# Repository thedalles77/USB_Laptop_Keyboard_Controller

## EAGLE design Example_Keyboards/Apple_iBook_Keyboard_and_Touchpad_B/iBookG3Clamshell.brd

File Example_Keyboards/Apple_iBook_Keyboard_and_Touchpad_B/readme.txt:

These Eagle layouts are for an obsolete Teensy 3.2 cutout board so should not be used for new builds. 
The Teensy 3.2 code is for a G3 Clamshell keyboard and a Dell PS/2 touchpad (not the original clamshell touchpad).
For new builds that use the Teensy 4.0, go to the iBookG3_Clamshell folder for board layouts and keyboard code given here.
https://github.com/thedalles77/USB_Laptop_Keyboard_Controller/tree/master/Example_Keyboards/iBookG3_Clamshell

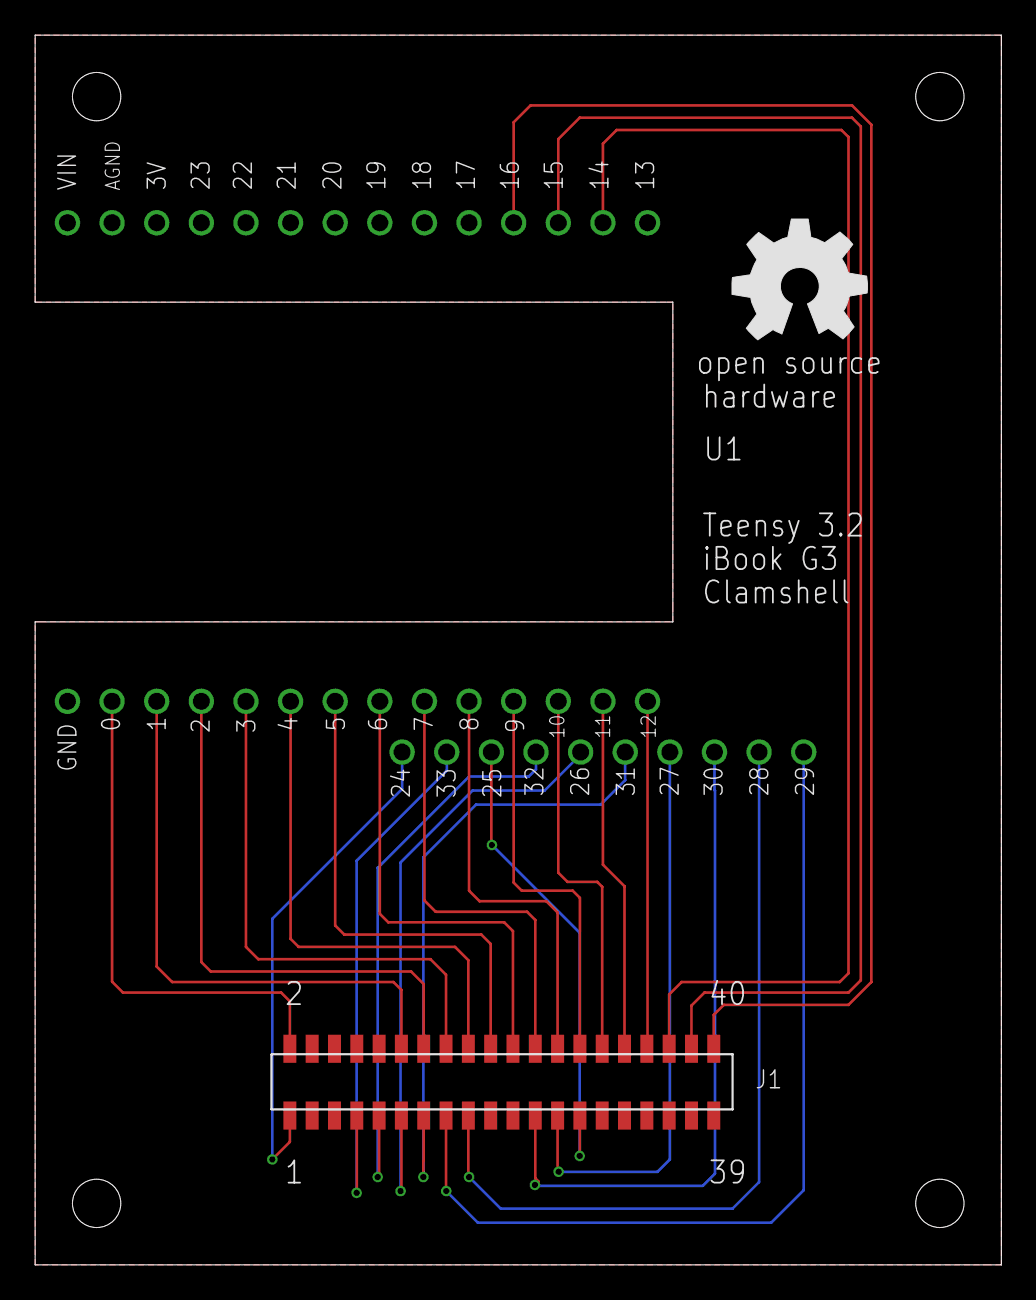
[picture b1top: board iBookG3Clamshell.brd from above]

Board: 2 copper layers, 55.0 x 70.0 mm, 3 parts (0 on the bottom side), 26 nets.

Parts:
J1: HDR127MET40FGVSMDR
U1: Teensy 3.2; TEENSY3P2CUTOUT
U$1: OSHW_8MM

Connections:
0: J1.P$2, U1.0
1: J1.P$12, U1.1
2: J1.P$14, U1.2
3: J1.P$16, U1.3
4: J1.P$18, U1.4
5: J1.P$20, U1.5
6: J1.P$22, U1.6
7: J1.P$24, U1.7
8: J1.P$26, U1.8
9: J1.P$28, U1.9
10: J1.P$30, U1.10
11: J1.P$32, U1.11
12: J1.P$34, U1.12
14: J1.P$36, U1.14
15: J1.P$38, U1.15
16: J1.P$40, U1.16
24: J1.P$1, U1.24
25: J1.P$27, U1.25
26: J1.P$11, U1.26
27: J1.P$25, U1.27
28: J1.P$17, U1.28
29: J1.P$15, U1.29
30: J1.P$23, U1.30
31: J1.P$13, U1.31
32: J1.P$9, U1.32
33: J1.P$7, U1.33

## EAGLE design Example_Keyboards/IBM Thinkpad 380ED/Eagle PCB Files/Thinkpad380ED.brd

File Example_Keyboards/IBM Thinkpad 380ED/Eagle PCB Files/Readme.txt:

To fabricate at OSHPark.com, send the .brd file to them. It will cost about $27 to fabricate 3 boards (includes USPS shipping in the US).

To fabricate at JLCPCB.com, send the .zip file to them. It will cost about $8 to fabricate and slow ship 5 boards to the US.

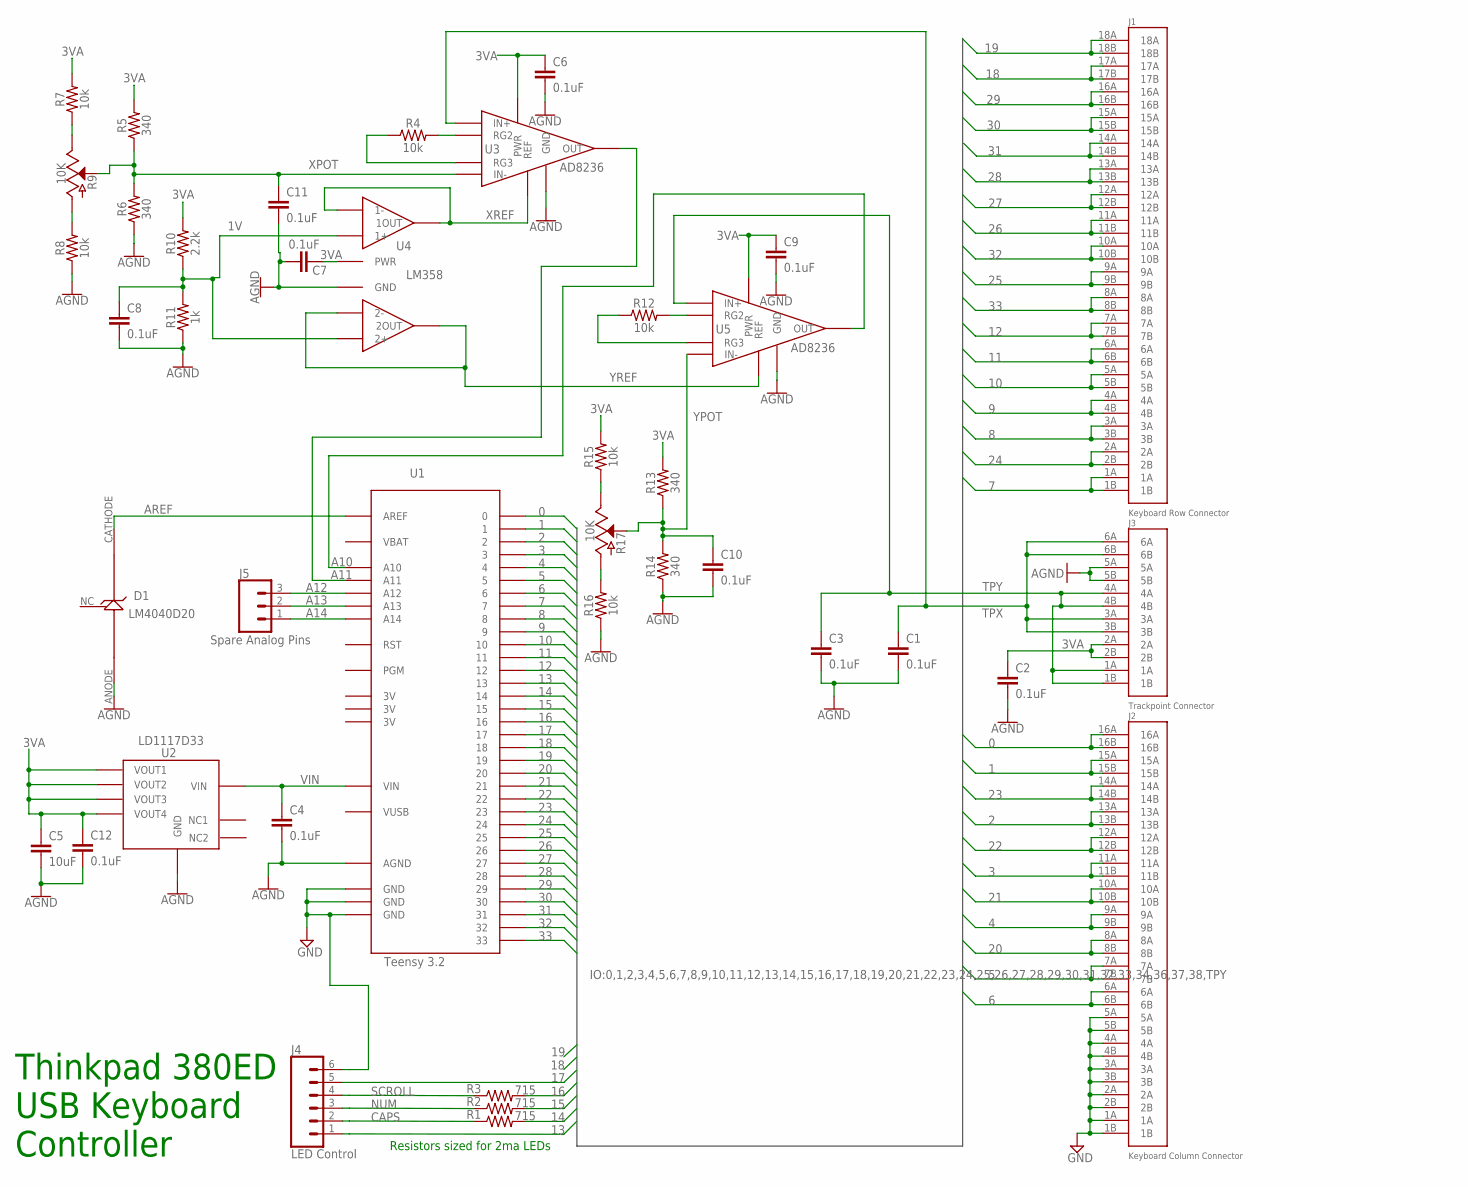
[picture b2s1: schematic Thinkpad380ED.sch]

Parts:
C1, C2, C3, C4, C6, C7, C8, C9, C10, C11, C12: 0.1uF; 0603
C5: 10uF; 0603
D1: LM4040D20; LM4040
J1: Keyboard Row Connector; 0526101833
J2: Keyboard Column Connector; 0526101633
J3: Trackpoint Connector; 0526100633
J4: LED Control; 1X06
J5: Spare Analog Pins; 1X03
R1, R2, R3: 715; 0603
R4, R7, R8, R12, R15, R16: 10k; 0603
R5, R6, R13, R14: 340; 0603
R9, R17: 10K; 3296W-1-103LF
R10: 2.2k; 0603
R11: 1k; 0603
U1: Teensy 3.2; TEENSY_3P2
U2: LD1117D33; LD1117D33CTR
U3, U5: AD8236
U4: LM358; LM358D

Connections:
0: J2.16A, J2.16B, U1.0
1: J2.15A, J2.15B, U1.1
1V: C8.1, R10.1, R11.2, U4.IN1+ (1+), U4.IN2+ (2+)
2: J2.13A, J2.13B, U1.2
3: J2.11A, J2.11B, U1.3
3VA: C2.1, C5.1, C6.1, C7.1, C9.1, C12.1, J3.2A, J3.2B, R5.2, R7.2, R10.2, R13.2, R15.2, U2.VOUT1, U2.VOUT2, U2.VOUT3, U2.VOUT4, U3.PWR, U4.PWR, U5.PWR
4: J2.9A, J2.9B, U1.4
5: J2.7A, J2.7B, U1.5
6: J2.6A, J2.6B, U1.6
7: J1.1A, J1.1B, U1.7
8: J1.3A, J1.3B, U1.8
9: J1.4A, J1.4B, U1.9
10: J1.5A, J1.5B, U1.10
11: J1.6A, J1.6B, U1.11
12: J1.7A, J1.7B, U1.12
13: J4.1, U1.13
14: R1.2, U1.14
15: R2.2, U1.15
16: R3.2, U1.16
17: J4.5, U1.17
18: J1.17A, J1.17B, U1.18
19: J1.18A, J1.18B, U1.19
20: J2.8A, J2.8B, U1.20
21: J2.10A, J2.10B, U1.21
22: J2.12A, J2.12B, U1.22
23: J2.14A, J2.14B, U1.23
24: J1.2A, J1.2B, U1.24
25: J1.9A, J1.9B, U1.25
26: J1.11A, J1.11B, U1.26
27: J1.12A, J1.12B, U1.27
28: J1.13A, J1.13B, U1.28
29: J1.16A, J1.16B, U1.29
30: J1.15A, J1.15B, U1.30
31: J1.14A, J1.14B, U1.31
32: J1.10A, J1.10B, U1.32
33: J1.8A, J1.8B, U1.33
A10: U1.A10, U5.VOUT (OUT)
A11: U1.A11, U3.VOUT (OUT)
A12: J5.3, U1.A12
A13: J5.2, U1.A13
A14: J5.1, U1.A14
AGND: C1.2, C2.2, C3.2, C4.2, C5.2, C6.2, C7.2, C8.2, C9.2, C10.2, C11.2, C12.2, D1.ANODE, J3.5A, J3.5B, R6.1, R8.1, R11.1, R14.1, R16.1, U1.AGND, U2.GND, U3.GND, U4.GND, U5.GND
AREF: D1.CATHODE, U1.AREF
CAPS: J4.2, R1.1
GND: J2.1A, J2.1B, J2.2A, J2.2B, J2.3A, J2.3B, J2.4A, J2.4B, J2.5A, J2.5B, J4.6, U1.GND1 (GND), U1.GND2 (GND), U1.GND3 (GND)
unnamed: R4.2, U3.RG2
unnamed: R4.1, U3.RG3
unnamed: R8.2, R9.A
unnamed: R7.1, R9.E
unnamed: R12.2, U5.RG2
unnamed: R12.1, U5.RG3
unnamed: R16.2, R17.A
unnamed: R15.1, R17.E
NUM: J4.3, R2.1
SCROLL: J4.4, R3.1
TPX: C1.1, J3.3A, J3.3B, J3.6A, J3.6B, U3.IN+
TPY: C3.1, J3.1A, J3.1B, J3.4A, J3.4B, U5.IN+
VIN: C4.1, U1.VIN, U2.VIN
XPOT: C11.1, R5.1, R6.2, R9.S, U3.IN-
XREF: U3.REF, U4.IN1- (1-), U4.OUT1 (1OUT)
YPOT: C10.1, R13.1, R14.2, R17.S, U5.IN-
YREF: U4.IN2- (2-), U4.OUT2 (2OUT), U5.REF

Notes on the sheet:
Thinkpad 380ED USB Keyboard Controller
Resistors sized for 2ma LEDs

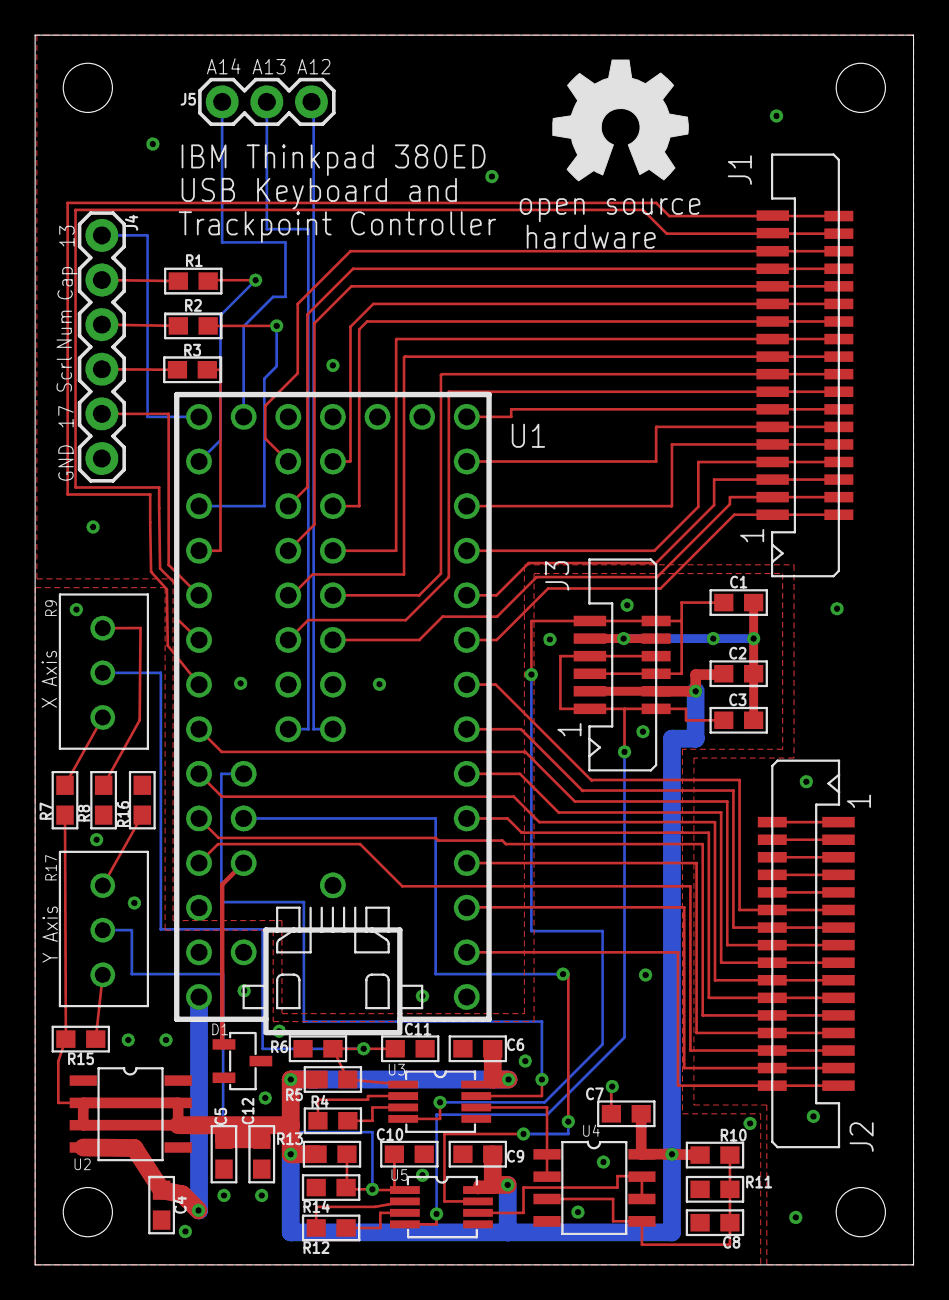
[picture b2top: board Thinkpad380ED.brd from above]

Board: 2 copper layers, 50.0 x 70.0 mm, 41 parts (0 on the bottom side), 62 nets.

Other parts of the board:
U$1: OSHW_8MM

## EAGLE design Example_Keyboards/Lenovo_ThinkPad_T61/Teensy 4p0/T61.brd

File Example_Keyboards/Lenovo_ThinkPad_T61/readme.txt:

These folders are for a Teensy T61 Thinkpad keyboard controller.

For a Raspberry Pi Pico T61 Thinkpad keyboard controller, go to this folder instead:
https://github.com/thedalles77/USB_Laptop_Keyboard_Controller/tree/master/Example_Keyboards/Pico_T61_Keyboard

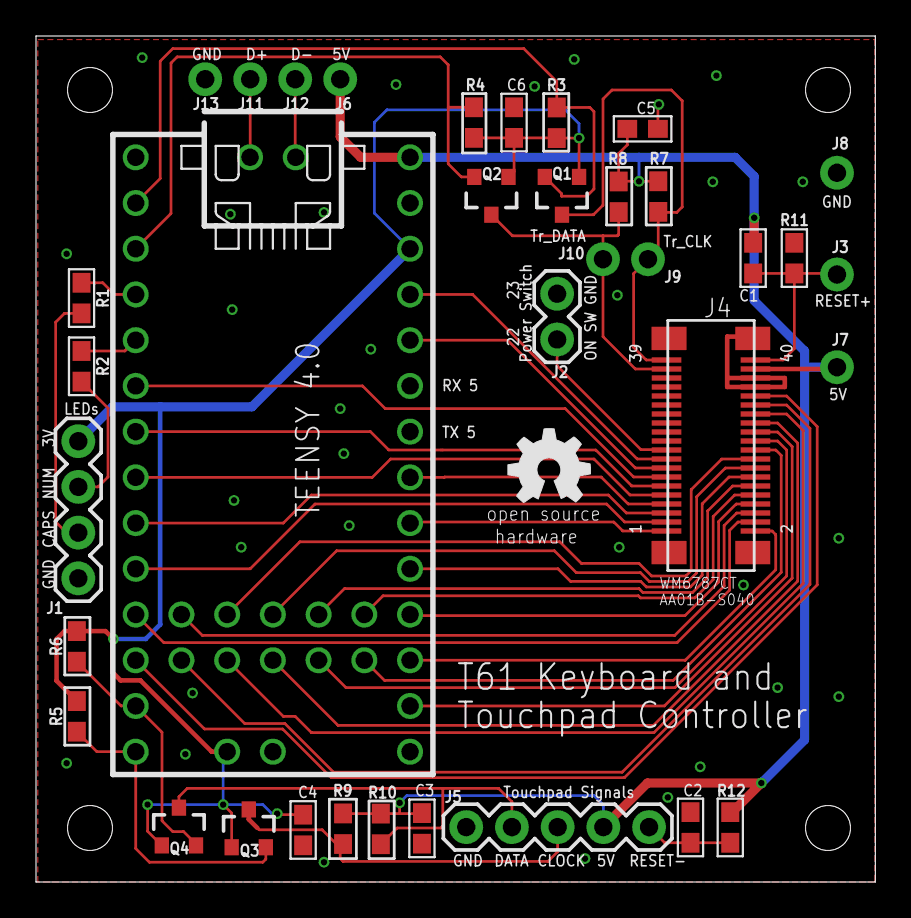
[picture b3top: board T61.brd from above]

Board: 2 copper layers, 46.6 x 47.0 mm, 38 parts (0 on the bottom side), 45 nets.

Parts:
C1, C2: 2.2UF; 0603_CAP
C3, C4, C5, C6: 0.1uf; 0603_CAP
J1: LEDs; 1X04
J2: Power Switch; 1X02
J3: RESET+; 1X01_NO_SILK
J4: AA01B-S040; WM6787_AA01B
J5: Touchpad_Signals; 1X05
J6, J7: 5V; 1X01_NO_SILK
J8, J13: GND; 1X01_NO_SILK
J9: TP_CLK; 1X01_NO_SILK
J10: TP_DATA; 1X01_NO_SILK
J11: D+; 1X01_NO_SILK
J12: D-; 1X01_NO_SILK
Q1, Q2, Q3, Q4: 220mA/50V/3.5Ω; SOT23-3
R1, R2: 715; 0603
R3, R4, R5, R6, R7, R8, R9, R10: 4.7k; 0603
R11: 100K; 0603_RESISTOR
R12: 17K; 0603_RESISTOR
U1: TEENSY4P0
U$1: OSHW_5MM
U$2: OSHW_16MM

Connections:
0: Q1.2, R3.1, U1.0
1: Q2.2, R4.1, U1.1
2: R1.1, U1.2
3: R2.1, U1.3
3V: C4.1, C6.1, J1.4, Q1.1, Q2.1, Q3.1, Q4.1, R3.2, R4.2, R5.2, R6.2, U1.3V, U1.3V1
4: J4.P$13, U1.4
5: J4.P$11, U1.5
5V: C1.1, C3.1, C5.1, J4.P$38, J5.4, J6.1, J7.1, R7.2, R8.2, R9.2, R10.2, R12.2, U1.5V
6: J4.P$9, U1.6
7: J4.P$5, U1.7
8: J4.P$3, U1.8
9: J4.P$4, U1.9
10: J4.P$32, U1.10
11: Q4.2, R6.1, U1.11
12: Q3.2, R5.1, U1.12
14: J4.P$24, U1.14
15: J4.P$2, U1.15
16: J4.P$8, U1.16
17: J4.P$14, U1.17
18: J4.P$1, U1.18
19: J4.P$7, U1.19
22: J4.P$15, U1.22
23: J4.P$17, U1.23
24: J4.P$20, U1.24
25: J4.P$10, U1.25
26: J4.P$22, U1.26
27: J4.P$12, U1.27
28: J4.P$26, U1.28
29: J4.P$16, U1.29
30: J4.P$28, U1.30
31: J4.P$18, U1.31
32: J4.P$30, U1.32
33: J4.P$6, U1.33
CAPS_LOCK: J1.2, R1.2
D+: J11.1, U1.D+
D-: J12.1, U1.D-
GND: C2.2, C3.2, C4.2, C5.2, C6.2, J1.1, J2.1, J4.P$31, J4.P$34, J4.P$36, J4.TAB1, J4.TAB2, J4.TAB3, J4.TAB4, J5.1, J8.1, J13.1, R11.1, U1.GND1, U1.GND2, U1.GND3
NUM_LOCK: J1.3, R2.2
ON: J2.2, J4.P$19
PAD_CLOCK: J5.3, Q3.3, R9.1
PAD_DATA: J5.2, Q4.3, R10.1
RESET+: C1.2, J3.1, J4.P$40, R11.2
RESET-: C2.1, J5.5, R12.1
TP_CLK: J4.P$39, J9.1, Q1.3, R7.1
TP_DATA: J4.P$37, J10.1, Q2.3, R8.1

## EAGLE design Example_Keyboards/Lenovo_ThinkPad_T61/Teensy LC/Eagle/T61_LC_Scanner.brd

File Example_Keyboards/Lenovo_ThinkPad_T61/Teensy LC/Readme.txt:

The Teensy LC is obsolete. Use the Teensy 4p0 for new builds.

The Lenovo_T61_keyboard_LC.ino code is just for the keyboard. Once you get it working, try the keyboard and TP (combined) code. 
If there's a problem communicating with the TP, it can make the keyboard code erratic and not work. Debug the TP connection problems separately.

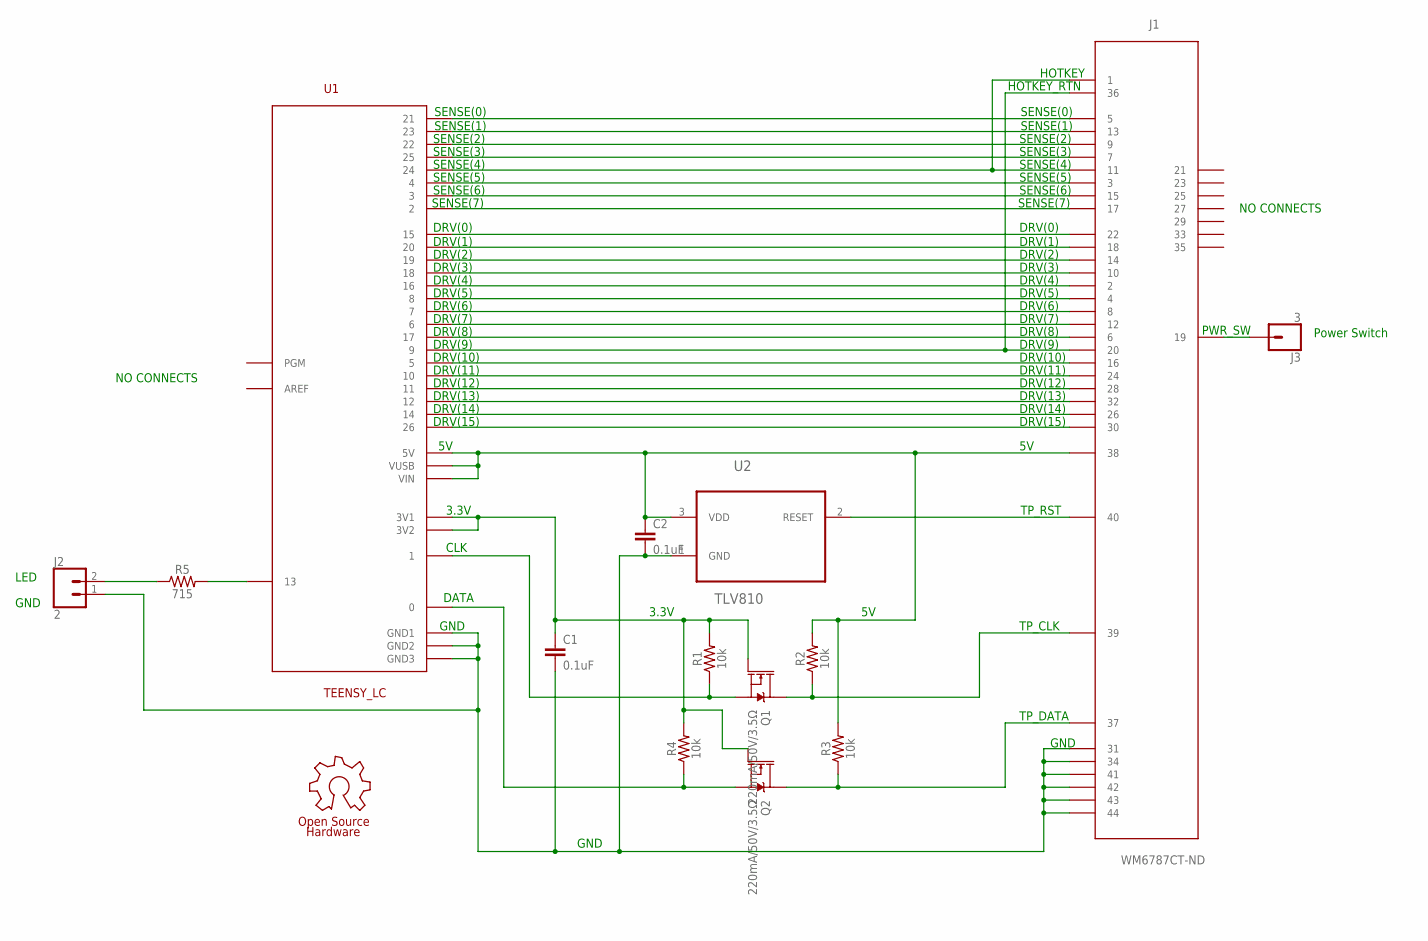
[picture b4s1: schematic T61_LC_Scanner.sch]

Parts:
C1, C2: 0.1uF; 0603
GOLD_ORB_SM1: OSHWLOGOLOGO5MM; OSHW_5MM
J1: WM6787CT-ND
J2: 2; 1X02
J3: 3; 1X01
Q1, Q2: 220mA/50V/3.5Ω; SOT23-3
R1, R2, R3, R4: 10k; 0603
R5: 715; 0603
U1: TEENSY_LC
U2: TLV810SDBZT; SOT95P237X112-3N

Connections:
3V: C1.1, Q1.1 (G), Q2.1 (G), R1.2, R4.2, U1.3V1, U1.3V2
5V: C2.1, J1.P$38 (38), R2.2, R3.2, U1.5V, U1.VIN, U1.VUSB, U2.3 (VDD)
CAPS_LCK: J2.2, R5.1
CLK: Q1.2 (S), R1.1, U1.1
DATA: Q2.2 (S), R4.1, U1.0
DRV(9): J1.P$20 (20), J1.P$36 (36), U1.9
GND: C1.2, C2.2, J1.P$31 (31), J1.P$34 (34), J1.P$41 (43), J1.P$42 (44), J1.P$43 (41), J1.P$44 (42), J2.1, U1.GND1, U1.GND2, U1.GND3, U2.1 (GND)
LED_13: R5.2, U1.13
unnamed: J1.P$5 (5), U1.21
unnamed: J1.P$13 (13), U1.23
unnamed: J1.P$9 (9), U1.22
unnamed: J1.P$7 (7), U1.25
unnamed: J1.P$3 (3), U1.4
unnamed: J1.P$15 (15), U1.3
unnamed: J1.P$17 (17), U1.2
unnamed: J1.P$22 (22), U1.15
unnamed: J1.P$18 (18), U1.20
unnamed: J1.P$14 (14), U1.19
unnamed: J1.P$10 (10), U1.18
unnamed: J1.P$2 (2), U1.16
unnamed: J1.P$4 (4), U1.8
unnamed: J1.P$8 (8), U1.7
unnamed: J1.P$12 (12), U1.6
unnamed: J1.P$6 (6), U1.17
unnamed: J1.P$16 (16), U1.5
unnamed: J1.P$24 (24), U1.10
unnamed: J1.P$28 (28), U1.11
unnamed: J1.P$32 (32), U1.12
unnamed: J1.P$26 (26), U1.14
unnamed: J1.P$30 (30), U1.26
PWR_SW: J1.P$19 (19), J3.1
SENSE(4): J1.P$1 (1), J1.P$11 (11), U1.24
TP_CLK: J1.P$39 (39), Q1.3 (D), R2.1
TP_DATA: J1.P$37 (37), Q2.3 (D), R3.1
TP_RST: J1.P$40 (40), U2.2 (RESET)

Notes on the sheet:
Power Switch
LED
GND
HOTKEY
HOTKEY_RTN
SENSE(0)
SENSE(1)
SENSE(2)
SENSE(3)
SENSE(4)
SENSE(5)
SENSE(6)
SENSE(7)
DRV(0)
DRV(1)
DRV(2)
DRV(3)
DRV(4)
DRV(5)
DRV(6)
DRV(7)
DRV(8)
DRV(9)
DRV(10)
DRV(11)
DRV(12)
DRV(13)
DRV(14)
DRV(15)
TP_RST
TP_CLK
TP_DATA
NO CONNECTS
PWR_SW
DATA
CLK
3.3V

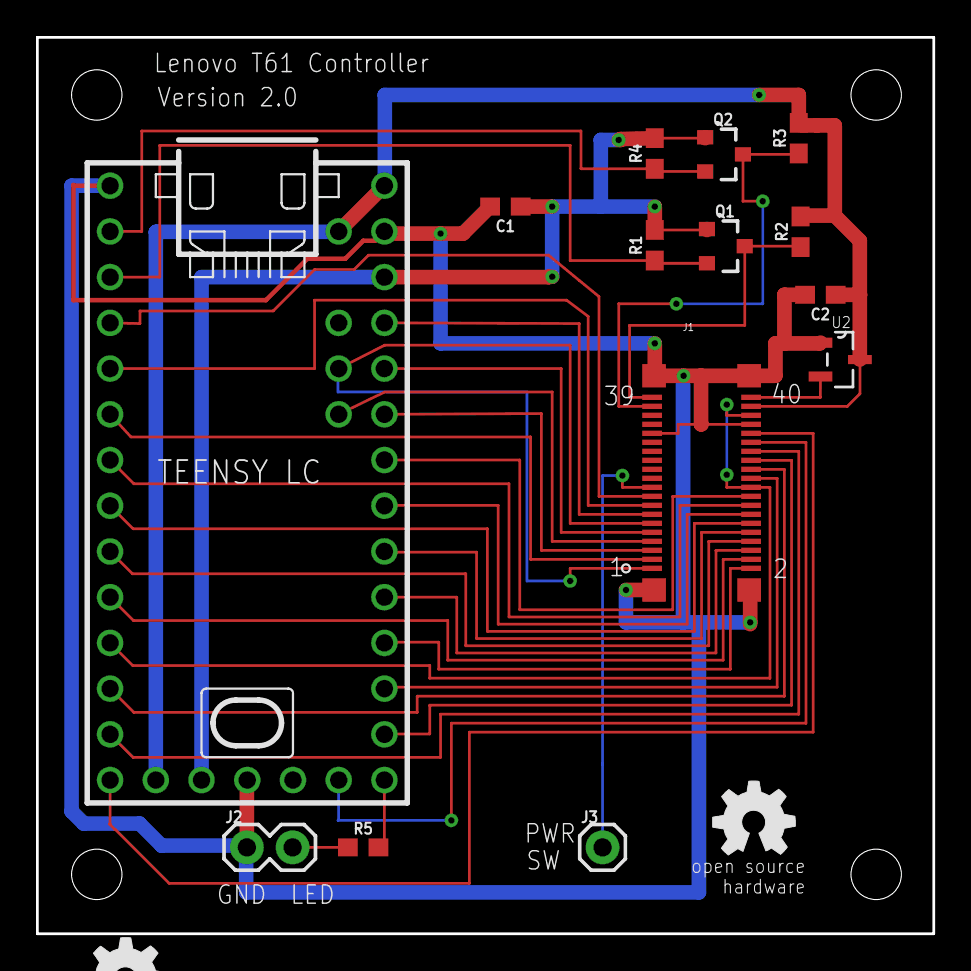
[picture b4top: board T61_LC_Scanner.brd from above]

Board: 2 copper layers, 49.8 x 49.8 mm, 16 parts (0 on the bottom side), 35 nets.

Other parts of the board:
U$1: OSHW_5MM

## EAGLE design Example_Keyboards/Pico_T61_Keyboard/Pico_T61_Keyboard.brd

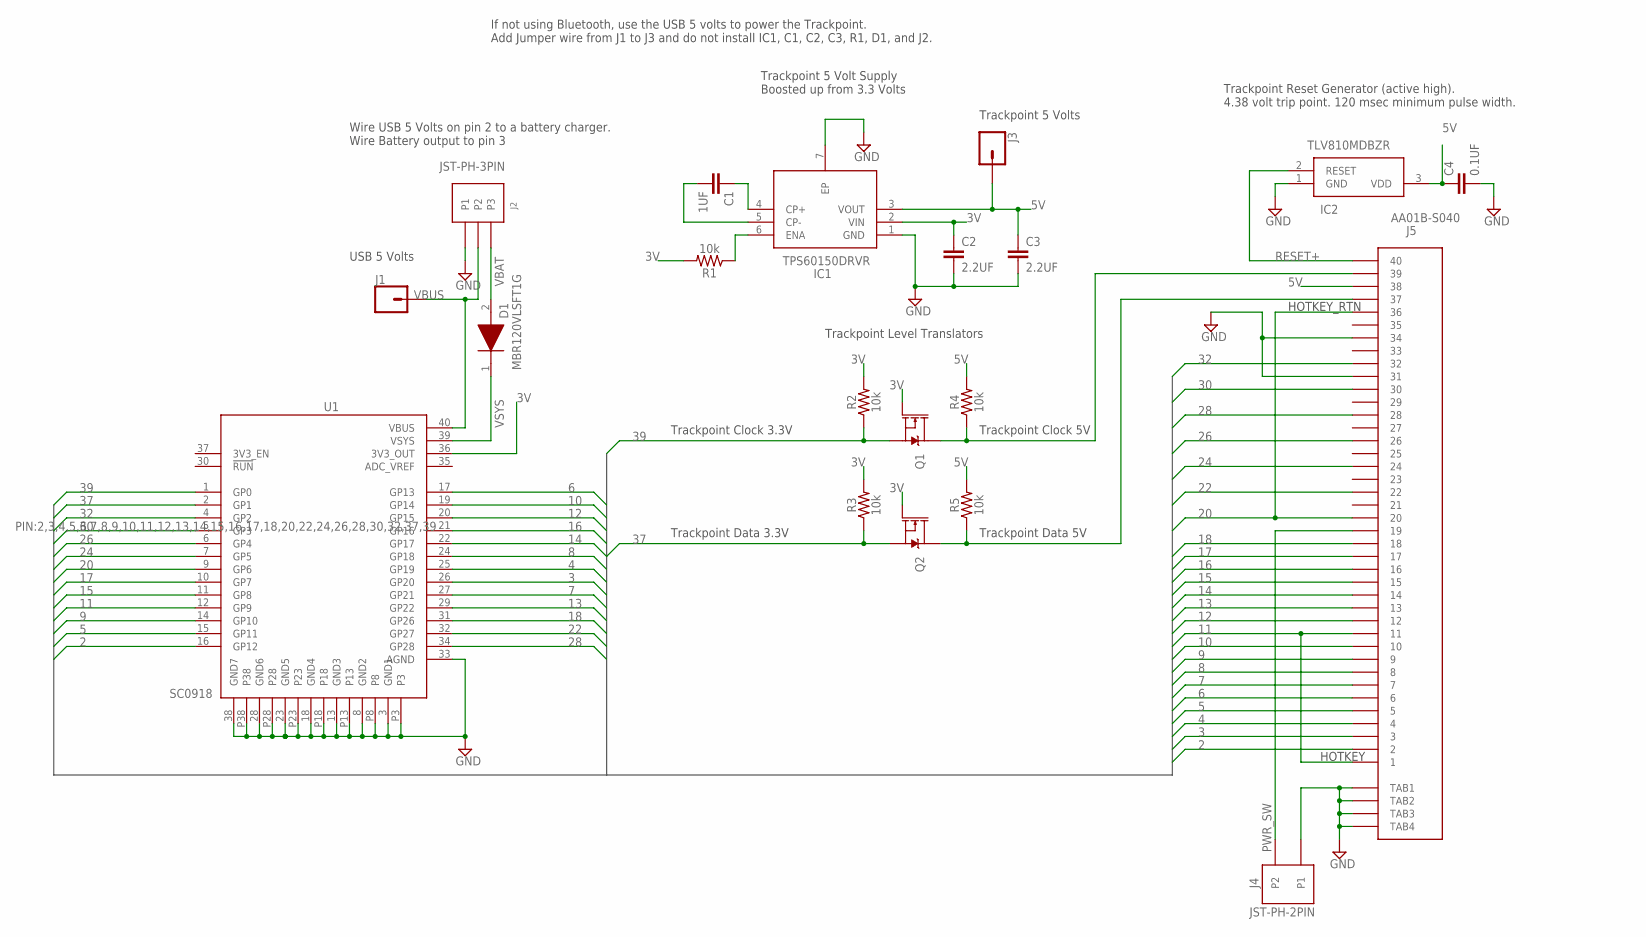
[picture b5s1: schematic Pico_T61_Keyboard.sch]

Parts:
C1: 1UF; 0603_CAP
C2, C3: 2.2UF; 0603_CAP
C4: 0.1UF; 0603_CAP
D1: MBR120VLSFT1G; SODFL3616X98N
IC1: TPS60150DRVR; SON65P200X200X80-7N
IC2: TLV810MDBZR; SOT95P237X112-3N
J1, J3: CONN_01PTH_NO_SILK_KIT; 1X01NS_KIT
J2: JST-PH-3PIN
J4: JST-PH-2PIN
J5: AA01B-S040; WM6787_AA01B
Q1, Q2: 220mA/50V/3.5Ω; SOT23-3
R1, R2, R3, R4, R5: 10k; 0603
U1: SC0918; MODULE_SC0918

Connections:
2: J5.P$2 (2), U1.16 (GP12)
3: J5.P$3 (3), U1.26 (GP20)
3V: C2.1, IC1.2 (VIN), Q1.1 (G), Q2.1 (G), R1.2, R2.2, R3.2, U1.36 (3V3_OUT)
4: J5.P$4 (4), U1.25 (GP19)
5: J5.P$5 (5), U1.15 (GP11)
5V: C3.1, C4.1, IC1.3 (VOUT), IC2.3 (VDD), J3.1, J5.P$38 (38), R4.2, R5.2
6: J5.P$6 (6), U1.17 (GP13)
7: J5.P$7 (7), U1.27 (GP21)
8: J5.P$8 (8), U1.24 (GP18)
9: J5.P$9 (9), U1.14 (GP10)
10: J5.P$10 (10), U1.19 (GP14)
11: J5.P$1 (1), J5.P$11 (11), U1.12 (GP9)
12: J5.P$12 (12), U1.20 (GP15)
13: J5.P$13 (13), U1.29 (GP22)
14: J5.P$14 (14), U1.22 (GP17)
15: J5.P$15 (15), U1.11 (GP8)
16: J5.P$16 (16), U1.21 (GP16)
17: J5.P$17 (17), U1.10 (GP7)
18: J5.P$18 (18), U1.31 (GP26)
20: J5.P$20 (20), J5.P$36 (36), U1.9 (GP6)
22: J5.P$22 (22), U1.32 (GP27)
24: J5.P$24 (24), U1.7 (GP5)
26: J5.P$26 (26), U1.6 (GP4)
28: J5.P$28 (28), U1.34 (GP28)
30: J5.P$30 (30), U1.5 (GP3)
32: J5.P$32 (32), U1.4 (GP2)
37: Q2.2 (S), R3.1, U1.2 (GP1)
39: Q1.2 (S), R2.1, U1.1 (GP0)
ADC_VREF: U1.35 (ADC_VREF)
GND: C2.2, C3.2, C4.2, IC1.1 (GND), IC1.7 (EP), IC2.1 (GND), J2.P$1 (P1), J4.P$1 (P1), J5.P$31 (31), J5.P$34 (34), J5.TAB1, J5.TAB2, J5.TAB3, J5.TAB4, U1.3 (GND1), U1.8 (GND2), U1.13 (GND3), U1.18 (GND4), U1.23 (GND5), U1.28 (GND6), U1.33 (AGND), U1.38 (GND7), U1.P3, U1.P8, U1.P13, U1.P18, U1.P23, U1.P28, U1.P38
unnamed: C1.1, IC1.4 (CP+)
unnamed: C1.2, IC1.5 (CP-)
unnamed: IC1.6 (ENA), R1.1
PWR_SW: J4.P$2 (P2), J5.P$19 (19)
RESET+: IC2.2 (RESET), J5.P$40 (40)
TP_CLK: J5.P$39 (39), Q1.3 (D), R4.1
TP_DATA: J5.P$37 (37), Q2.3 (D), R5.1
VBAT: D1.2 (A), J2.P$3 (P3)
VBUS: J1.1, J2.P$2 (P2), U1.40 (VBUS)
VSYS: D1.1 (K), U1.39 (VSYS)

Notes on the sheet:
Trackpoint Clock 3.3V
Trackpoint Data 3.3V
Trackpoint Clock 5V
Trackpoint Data 5V
Trackpoint Level Translators
HOTKEY
HOTKEY_RTN
Trackpoint 5 Volt Supply Boosted up from 3.3 Volts
Trackpoint Reset Generator (active high). 4.38 volt trip point. 120 msec minimum pulse width.
Wire USB 5 Volts on pin 2 to a battery charger. Wire Battery output to pin 3
USB 5 Volts
Trackpoint 5 Volts
If not using Bluetooth, use the USB 5 volts to power the Trackpoint. Add Jumper wire from J1 to J3 and do not install IC1, C1, C2, C3, R1, D1, and J2.

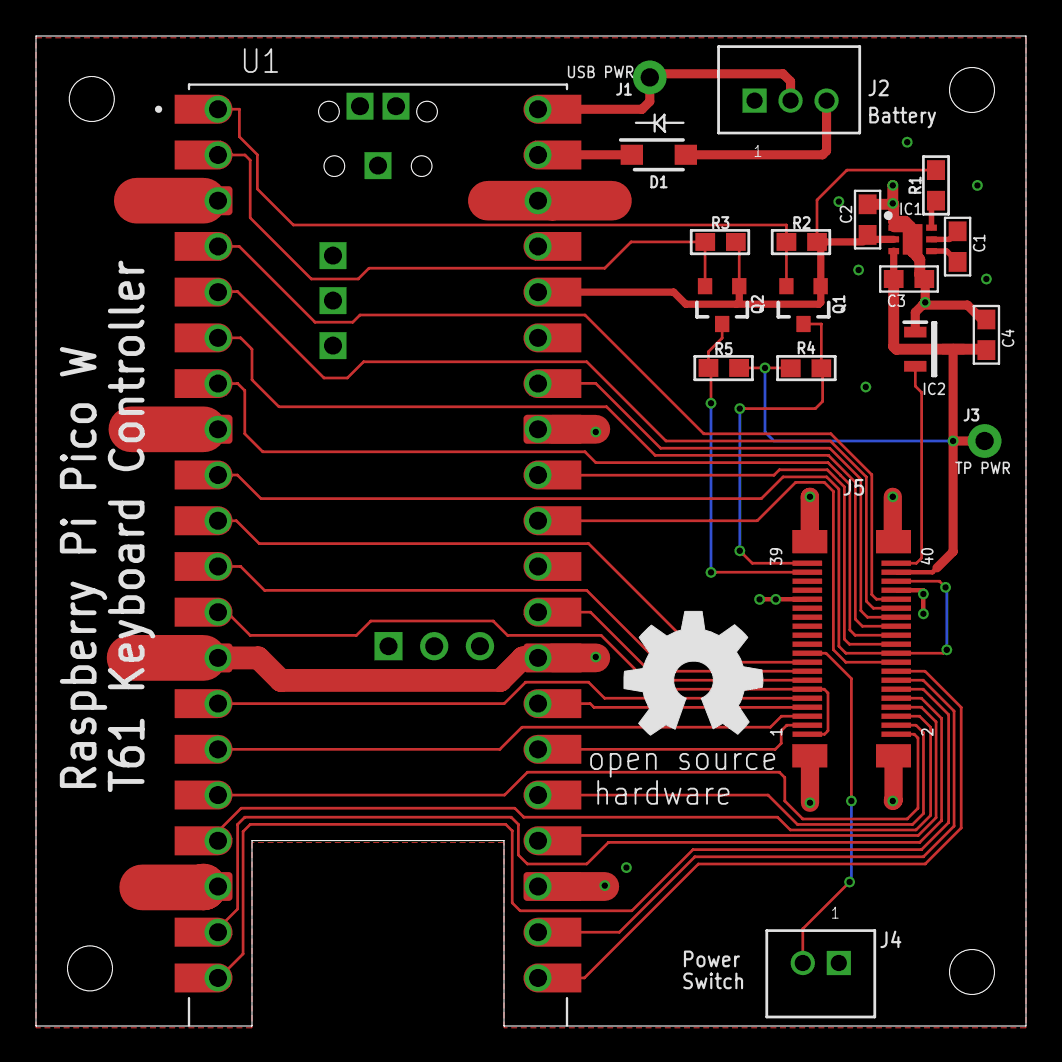
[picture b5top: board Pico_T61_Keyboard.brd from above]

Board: 2 copper layers, 55.0 x 55.0 mm, 22 parts (0 on the bottom side), 39 nets.

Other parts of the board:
U$1, U$2: OSHW_8MM

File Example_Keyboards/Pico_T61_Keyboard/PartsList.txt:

Partlist for Pico_T61_Keyboard

Qty Value          Device                 Package             Parts              Description                                                                                                                                         
2   None           CONN_01PTH_NO_SILK_KIT 1X01NS_KIT          J1, J3             Single connection point used for jumper wire.                           
1   0.1UF          0603_CAP               0603_CAP            C4                 Bypass cap for reset generator IC                                       
5   10k            10KOHM-0603-1/10W-1%   0603                R1, R2, R3, R4, R5 10KΩ 0603 size resistor                                                 
1   1UF            0603_CAP               0603_CAP            C1                 1uF X7R 0603 size capacitor                                             
2   2.2UF          0603_CAP               0603_CAP            C2, C3             2.2uF X7R 0603 size capacitor                                           
2   220mA/50V/3.5Ω MOSFET-NCH-BSS138      SOT23-3             Q1, Q2             BSS138 N-channel MOSFET                                                 
1   AA01B-S040     AA01B-S040             AA01B-S040          J5                 40 Pin Keyboard Connector                                               
1   JST-PH-2PIN    JST-PH-2PIN            JST-PH-2PIN         J4                 2 Pin JST Connector                                                     
1   JST-PH-3PIN    JST-PH-3PIN            JST-PH-3PIN         J2                 4 Pin JST Connector                                                     
1   MBR120VLSFT1G  MBR120VLSFT1G          SODFL3616X98N       D1                 Diode Schottky 20V 1A SOD123FL ON Semi MBR120VLSFT1G                    
1   SC0918         SC0918                 MODULE_SC0918       U1                 Raspberry Pi Pico W (with or without header pins)                       
1   TLV810MDBZR    TLV810MDBZR            SOT95P237X112-3N    IC2                3-pin voltage supervisor (reset IC) with active-high, push-pull output  
1   TPS60150DRVR   TPS60150DRVR           SON65P200X200X80-7N IC1                140mA, 5V Charge Pump in 2x2 SON

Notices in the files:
parts and their libraries:
SparkFun-Connectors: Licensing: Creative Commons ShareAlike 4.0 International - https://creativecommons.org/licenses/by-sa/4.0
